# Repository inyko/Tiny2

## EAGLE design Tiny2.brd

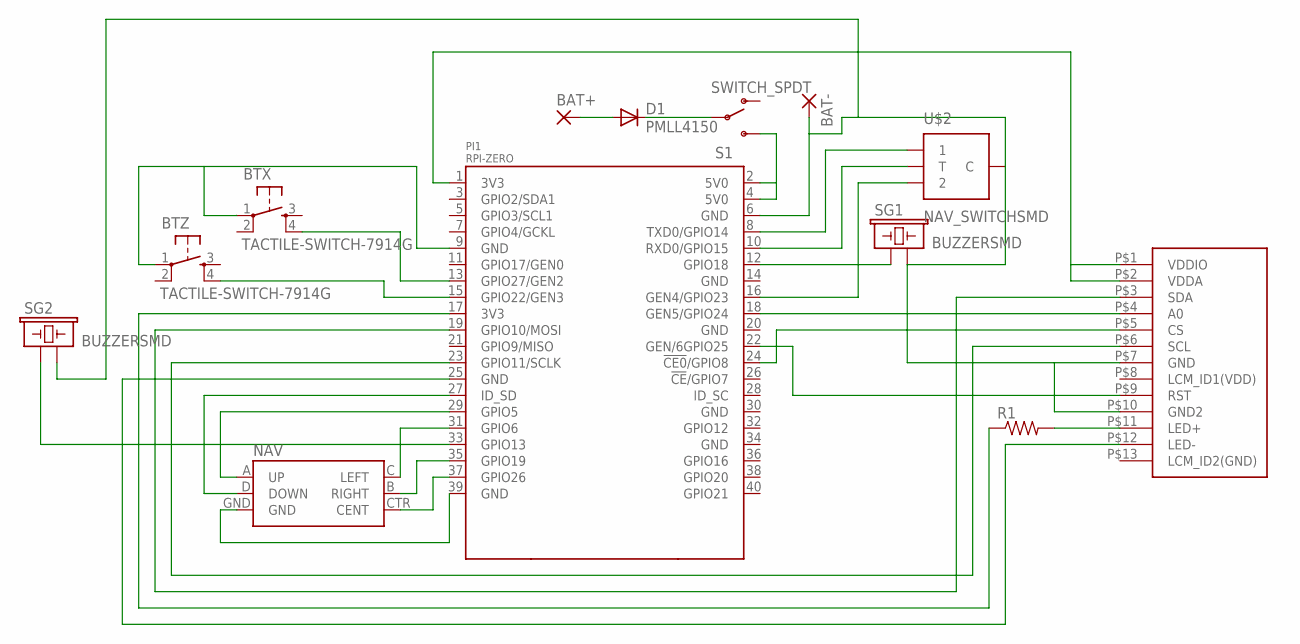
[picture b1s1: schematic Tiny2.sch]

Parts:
BAT+: SMD5; SMD2,54-5,08
BAT-: SMD5; SMD2,54-5,08
BTX: TACTILE-SWITCH-7914G; 7914G
BTZ: TACTILE-SWITCH-7914G; 7914G
D1: PMLL4150; SOD80C
NAV: JOYSTICK_MINI
PI1: RPI-ZERO; RASPBERRYPI_BASTELSTUBE_V13_RASPI_BOARD_B+_FULL
R1: RESISTOR0805-RES; 0805
S1: SWITCH_SPDT; KPS-1290
SG1, SG2: BUZZERSMD; BUZZER-CMT1603
U$1: ST7735S-1.44
U$2: NAV_SWITCHSMD; NAV_SWITCH

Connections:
3V3@1: PI1.1 (3V3), U$1.P$1 (VDDIO), U$1.P$2 (VDDA)
3V3@2: PI1.17 (3V3), R1.1
5V0@2: PI1.2 (5V0), PI1.4 (5V0), S1.S
GND@1: BTX.1, BTZ.1, PI1.9 (GND)
GND@2: PI1.25 (GND), U$1.P$12 (LED-)
GND@3: NAV.GND, PI1.39 (GND)
GND@8: BAT-.1, PI1.6 (GND), SG1.P$2 (2), SG2.P$2 (2), U$1.P$7 (GND), U$1.P$10 (GND2), U$2.C
unnamed: PI1.22 (GEN/6GPIO25), U$1.P$9 (RST)
unnamed: PI1.23 (GPIO11/SCLK), U$1.P$6 (SCL)
unnamed: PI1.19 (GPIO10/MOSI), U$1.P$3 (SDA)
unnamed: NAV.CTR (CENT), PI1.37 (GPIO26)
unnamed: NAV.B (RIGHT), PI1.35 (GPIO19)
unnamed: PI1.18 (GEN5/GPIO24), U$1.P$4 (A0)
unnamed: PI1.24 (!CE0!/GPIO8), U$1.P$5 (CS)
unnamed: NAV.C (LEFT), PI1.31 (GPIO6)
unnamed: NAV.A (UP), PI1.29 (GPIO5)
unnamed: NAV.D (DOWN), PI1.27 (ID_SD)
unnamed: BTZ.4, PI1.15 (GPIO22/GEN3)
unnamed: BTX.4, PI1.13 (GPIO27/GEN2)
unnamed: PI1.12 (GPIO18), SG1.P$1 (1)
unnamed: R1.2, U$1.P$11 (LED+)
unnamed: PI1.33 (GPIO13), SG2.P$1 (1)
unnamed: PI1.8 (TXD0/GPIO14), U$2.1
unnamed: PI1.10 (RXD0/GPIO15), U$2.T
unnamed: PI1.16 (GEN4/GPIO23), U$2.2

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
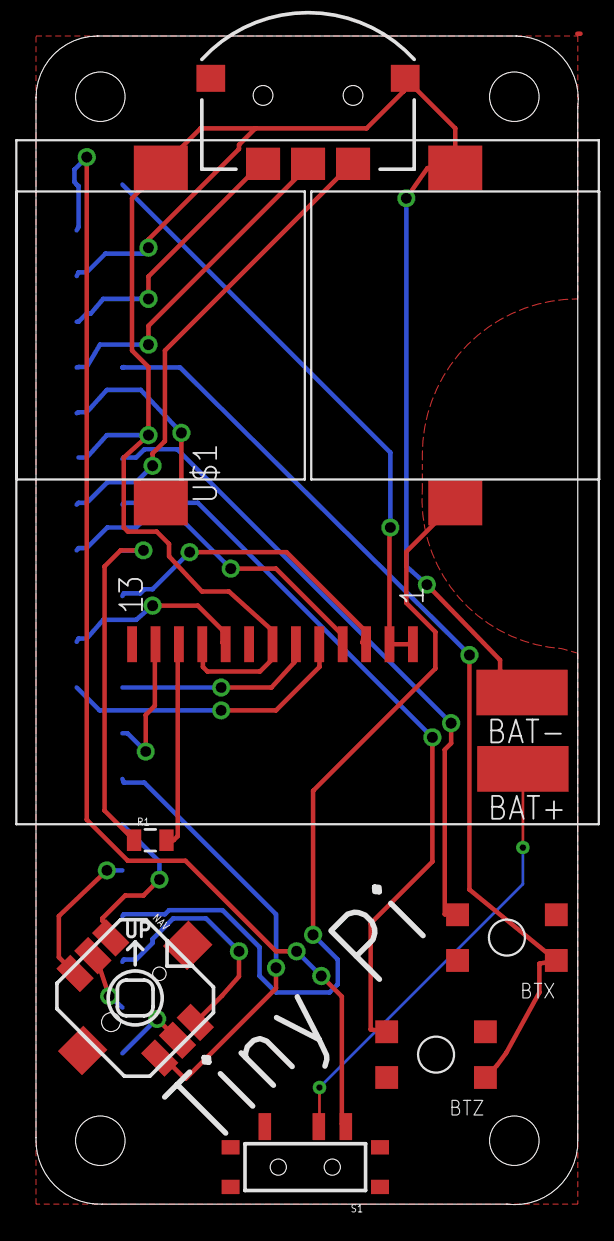
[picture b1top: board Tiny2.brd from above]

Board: 2 copper layers, 30.1 x 64.9 mm, 12 parts (1 on the bottom side), 26 nets.

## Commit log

2017-05-26 Add files via upload
    just popping the button cfg for retrogame, and the boot/config.txt for reference later
2017-06-25 added drawings, fixed board
2017-11-10 removed diode, cleaned up some vias inside the header section
2017-11-15 added some gerbers
2018-02-08 some gerber files for chinafab

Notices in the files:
parts and their libraries:
SparkFun-Electromechanical: Licensing: Creative Commons ShareAlike 4.0 International - https://creativecommons.org/licenses/by-sa/4.0
